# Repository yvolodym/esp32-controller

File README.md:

## Controller

ESP32-WROVER based wireless game controller. Two resistive (potentiometer)
analog joysticks plus an ST7789 SPI display, transmitting over ESP-NOW.
Firmware uses native ESP-IDF — see `CLAUDE.md` for architecture and pin
layout details.

### References

#### ESP-NOW
* https://randomnerdtutorials.com/esp32-cyd-esp-now-receive-data/
* https://habr.com/ru/companies/beget/articles/929336/
* https://wolles-elektronikkiste.de/esp-now
* https://github.com/SolderedElectronics/USB-UART-CH340C-converter-board-hardware-design

#### Joysticks (resistive thumbstick modules)
* https://tech.alpsalpine.com/e/products/detail/RKJXV122400R/
* https://github.com/dbenoy/thumbstick-breakout/blob/main/docs/board.png

#### LiPo charging module
* https://elektro.turanis.de/html/prj224/index.html

### Pin assignments

`CLAUDE.md` is the source of truth — the lists below are a quick reference.
All pins verified against `kicad/esp32-controller.kicad_sch` and
`kicad/supply.kicad_sch`.

#### ST7789 display (J1, 8-pin header — VSPI)

| J1 pin | Signal | GPIO |
|---|---|---|
| 1 | BL (backlight) | GPIO15 |
| 2 | CS  | GPIO5  |
| 3 | DC  | GPIO2  |
| 4 | RST | GPIO4  |
| 5 | MOSI / SDA | GPIO23 |
| 6 | SCK / SCL  | GPIO18 |
| 7 | VCC | +3.3 V |
| 8 | GND | GND |

#### Joystick 1 — RIGHT stick (U2 in schematic)

| Signal | GPIO | ADC |
|---|---|---|
| VRx (X axis) | GPIO32 | ADC1_CH4 |
| VRy (Y axis) | GPIO33 | ADC1_CH5 |
| Button (SEL) | GPIO25 | — *(not wired in hardware, see CLAUDE.md)* |

#### Joystick 2 — LEFT stick (U3 in schematic)

| Signal | GPIO | ADC |
|---|---|---|
| HRx (X axis) | GPIO34 | ADC1_CH6 |
| HRy (Y axis) | GPIO35 | ADC1_CH7 |
| Button (SEL) | GPIO26 | — *(not wired in hardware, see CLAUDE.md)* |

#### Battery sense

| Signal | GPIO | ADC |
|---|---|---|
| VBAT divider (R17 220 kΩ / R18 100 kΩ, net `HVBAT`) | GPIO36 (SENSOR_VP) | ADC1_CH0 |

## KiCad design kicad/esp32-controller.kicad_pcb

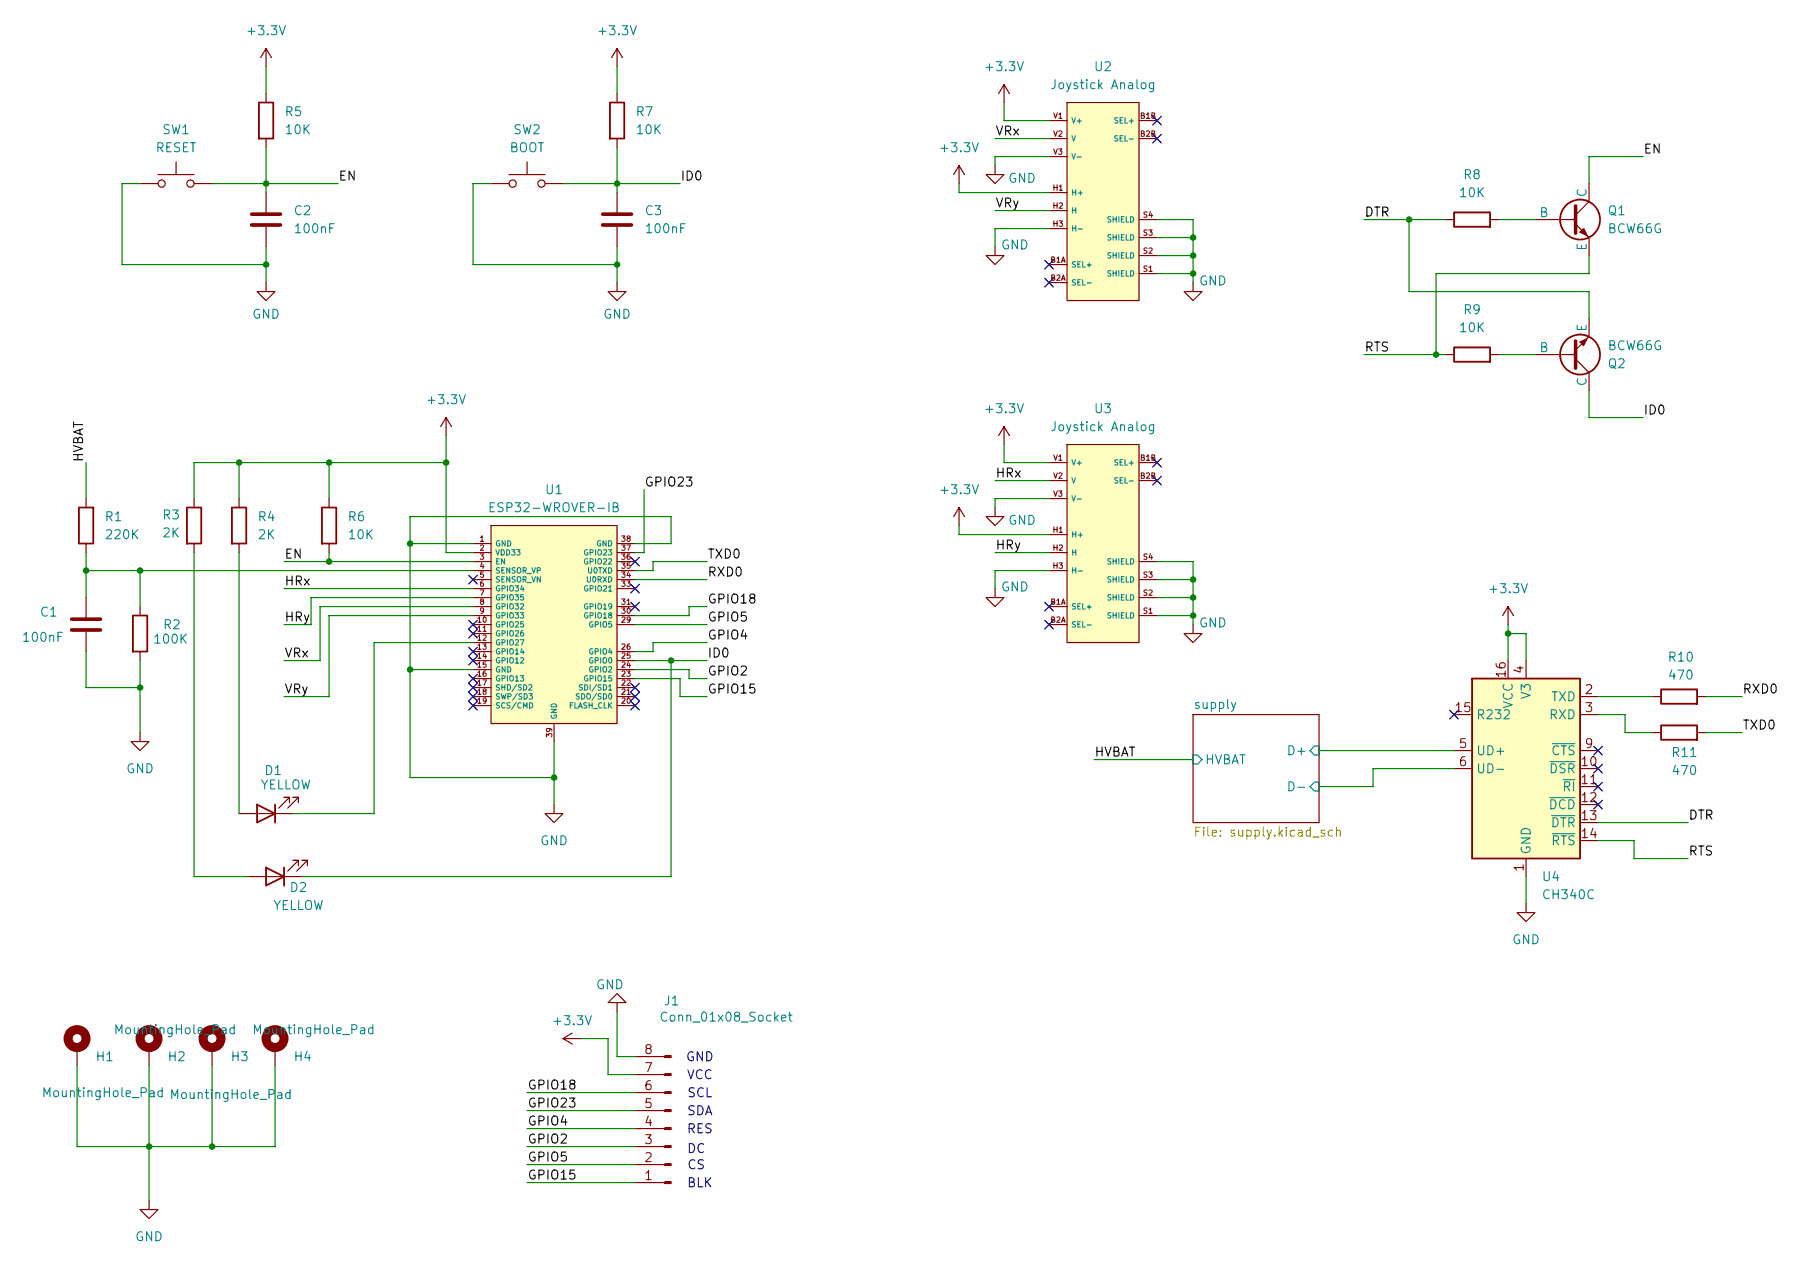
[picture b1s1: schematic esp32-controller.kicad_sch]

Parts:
C1, C2, C3: 100nF; C_1206_3216Metric
D1, D2: YELLOW; D_0603_1608Metric
H1, H2, H3, H4: MountingHole_Pad; MountingHole_2.7mm_Pad_Via
J1: Conn_01x08_Socket; PinSocket_1x08_P2.54mm_Vertical
Q1, Q2: BCW66G; SOT-23
R1: 220K; R_1206_3216Metric
R2: 100K; R_1206_3216Metric
R3, R4: 2K; R_1206_3216Metric
R5, R6, R7: 10K; R_1206_3216Metric
R8, R9: 10K; R_1206_3216Metric; LCSC C25819
R10, R11: 470; R_1206_3216Metric; LCSC C25819
SW1: RESET; SW_PUSH_1P1T_6x3.5mm_H4.3_APEM_MJTP1243
SW2: BOOT; SW_PUSH_1P1T_6x3.5mm_H4.3_APEM_MJTP1243
U1: ESP32-WROVER-IB
U2, U3: Joystick Analog; Joystick_Analog
U4: CH340C; SOIC-16_3.9x9.9mm_P1.27mm

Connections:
+3.3V: J1.7, R3.1, R4.1, R5.1, R6.1, R7.1, U1.2 (VDD33), U2.H1 (H+), U2.V1 (V+), U3.H1 (H+), U3.V1 (V+), U4.4 (V3), U4.16 (VCC); also elsewhere on the board
/DTR: Q2.3 (E), R8.1, U4.13 (~DTR)
/EN: C2.1, Q1.1 (C), R5.2, R6.2, SW1.2, U1.3 (EN)
/GPIO2: J1.3, U1.24 (GPIO2)
/GPIO4: J1.4, U1.26 (GPIO4)
/GPIO5: J1.2, U1.29 (GPIO5)
/GPIO15: J1.1, U1.23 (GPIO15)
/GPIO18: J1.6, U1.30 (GPIO18)
/GPIO23: J1.5, U1.37 (GPIO23)
/HRx: U1.6 (GPIO34), U3.V2 (V)
/HRy: U1.7 (GPIO35), U3.H2 (H)
/HVBAT: R1.2; also elsewhere on the board
/ID0: C3.1, D2.1 (K), Q2.1 (C), R7.2, SW2.2, U1.25 (GPIO0)
/RTS: Q1.3 (E), R9.1, U4.14 (~RTS)
/RXD0: R10.2, U1.34 (U0RXD)
/TXD0: R11.2, U1.35 (U0TXD)
/VRx: U1.8 (GPIO32), U2.V2 (V)
/VRy: U1.9 (GPIO33), U2.H2 (H)
/supply/D+: U4.5 (UD+); also elsewhere on the board
/supply/D-: U4.6 (UD-); also elsewhere on the board
GND: C1.2, C2.2, C3.2, H1.1, H2.1, H3.1, H4.1, J1.8, R2.2, SW1.1, SW2.1, U1.1 (GND), U1.15 (GND), U1.38 (GND), U1.39 (GND), U2.H3 (H-), U2.S1 (SHIELD), U2.S2 (SHIELD), U2.S3 (SHIELD), U2.S4 (SHIELD), U2.V3 (V-), U3.H3 (H-), U3.S1 (SHIELD), U3.S2 (SHIELD), U3.S3 (SHIELD), U3.S4 (SHIELD), U3.V3 (V-), U4.1 (GND); also elsewhere on the board
unnamed: D1.2 (A), R4.2
unnamed: D1.1 (K), U1.12 (GPIO27)
unnamed: D2.2 (A), R3.2
unnamed: Q1.2 (B), R8.2
unnamed: Q2.2 (B), R9.2
unnamed: C1.1, R1.1, R2.1, U1.4 (SENSOR_VP)
unnamed: R11.1, U4.3 (RXD)
unnamed: R10.1, U4.2 (TXD)

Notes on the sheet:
RES
VCC
SCL
GND
BLK
SDA

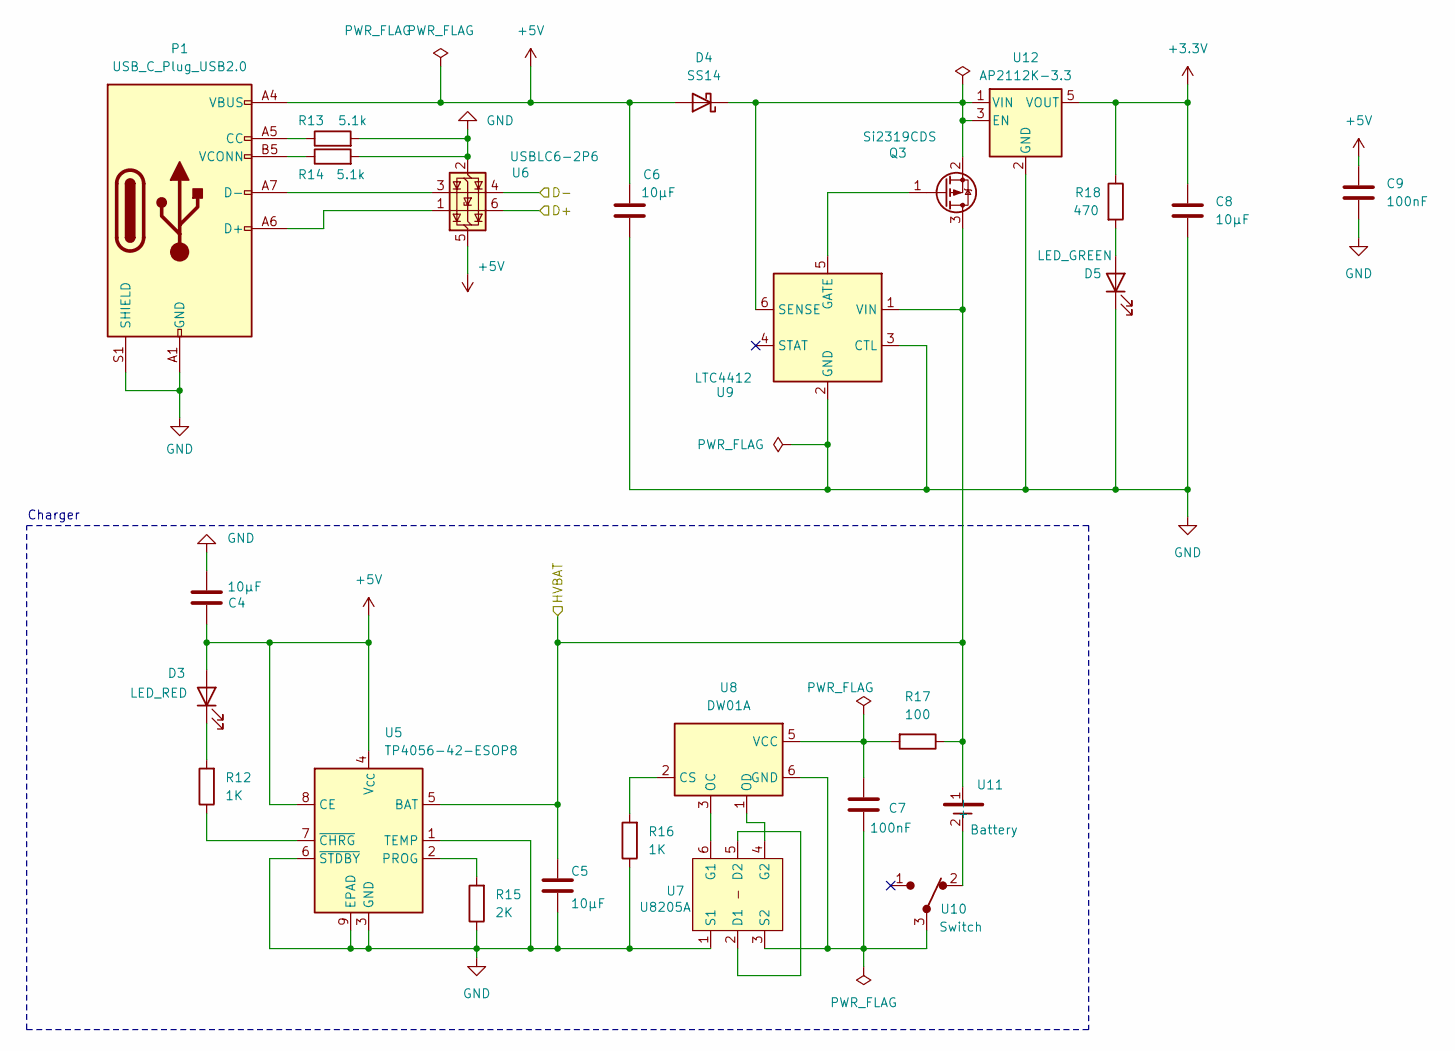
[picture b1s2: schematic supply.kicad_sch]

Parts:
C4, C5, C6, C8: 10µF; C_1206_3216Metric
C7, C9: 100nF; C_1206_3216Metric
D3: LED_RED; LED_D2.0mm_W4.8mm_H2.5mm_FlatTop
D4: SS14; D_SMA
D5: LED_GREEN; LED_D2.0mm_W4.8mm_H2.5mm_FlatTop
P1: USB_C_Plug_USB2.0; USB_C_Receptacle_GCT_USB4105-xx-A_16P_TopMnt_Horizontal; LCSC C456012
Q3: Si2319CDS; SOT-23
R12, R16: 1K; R_1206_3216Metric
R13, R14: 5.1k; R_1206_3216Metric
R15: 2K; R_1206_3216Metric
R17: 100; R_1206_3216Metric
R18: 470; R_1206_3216Metric
U5: TP4056-42-ESOP8; SOIC-8-1EP_3.9x4.9mm_P1.27mm_EP2.41x3.3mm_ThermalVias
U6: USBLC6-2P6; SOT-23-6
U7: U8205A; SOT-23-6
U8: DW01A; SOT-23-6
U9: LTC4412; TSOT-23-6
U10: Switch; SW_SPDT_PCM12
U11: Battery; NCR18650B
U12: AP2112K-3.3; SOT-23-5

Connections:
+3.3V: C8.1, R18.1, U12.5 (VOUT); also elsewhere on the board
+5V: C4.1, C6.1, C9.2, D3.2 (A), D4.2 (A), P1.A4 (VBUS), P1.A9 (VBUS), P1.B4 (VBUS), P1.B9 (VBUS), U5.4 (V_{CC}), U5.8 (CE), U6.5 (VBUS)
/HVBAT: C5.1, Q3.3 (D), R17.1, U5.5 (BAT), U9.1 (VIN), U11.1 (+); also elsewhere on the board
/supply/D+: U6.6 (I/O1); also elsewhere on the board
/supply/D-: U6.4 (I/O2); also elsewhere on the board
GND: C4.2, C5.2, C6.2, C8.2, C9.1, D5.1 (K), P1.A1 (GND), P1.A12 (GND), P1.B1 (GND), P1.B12 (GND), P1.S1 (SHIELD), R13.2, R14.2, R15.1, R16.1, U5.1 (TEMP), U5.3 (GND), U5.6 (~STDBY), U5.9 (EPAD), U6.2 (GND), U7.1 (S1), U9.2 (GND), U9.3 (CTL), U12.2 (GND); also elsewhere on the board
unnamed: D3.1 (K), R12.2
unnamed: D4.1 (K), Q3.2 (S), U9.6 (SENSE), U12.1 (VIN), U12.3 (EN)
unnamed: D5.2 (A), R18.2
unnamed: P1.A5 (CC), R13.1
unnamed: P1.A6 (D+), U6.1 (I/O1)
unnamed: P1.A7 (D-), U6.3 (I/O2)
unnamed: P1.B5 (VCONN), R14.1
unnamed: Q3.1 (G), U9.5 (GATE)
unnamed: R15.2, U5.2 (PROG)
unnamed: R12.1, U5.7 (~CHRG)
unnamed: U7.2 (D1), U7.5 (D2)
unnamed: U7.6 (G1), U8.3 (OC)
unnamed: U7.4 (G2), U8.1 (OD)
unnamed: C7.1, U7.3 (S2), U8.6 (GND), U10.3
unnamed: R16.2, U8.2 (CS)
unnamed: C7.2, R17.2, U8.5 (VCC)
unnamed: U10.2, U11.2 (-)

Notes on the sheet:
Charger

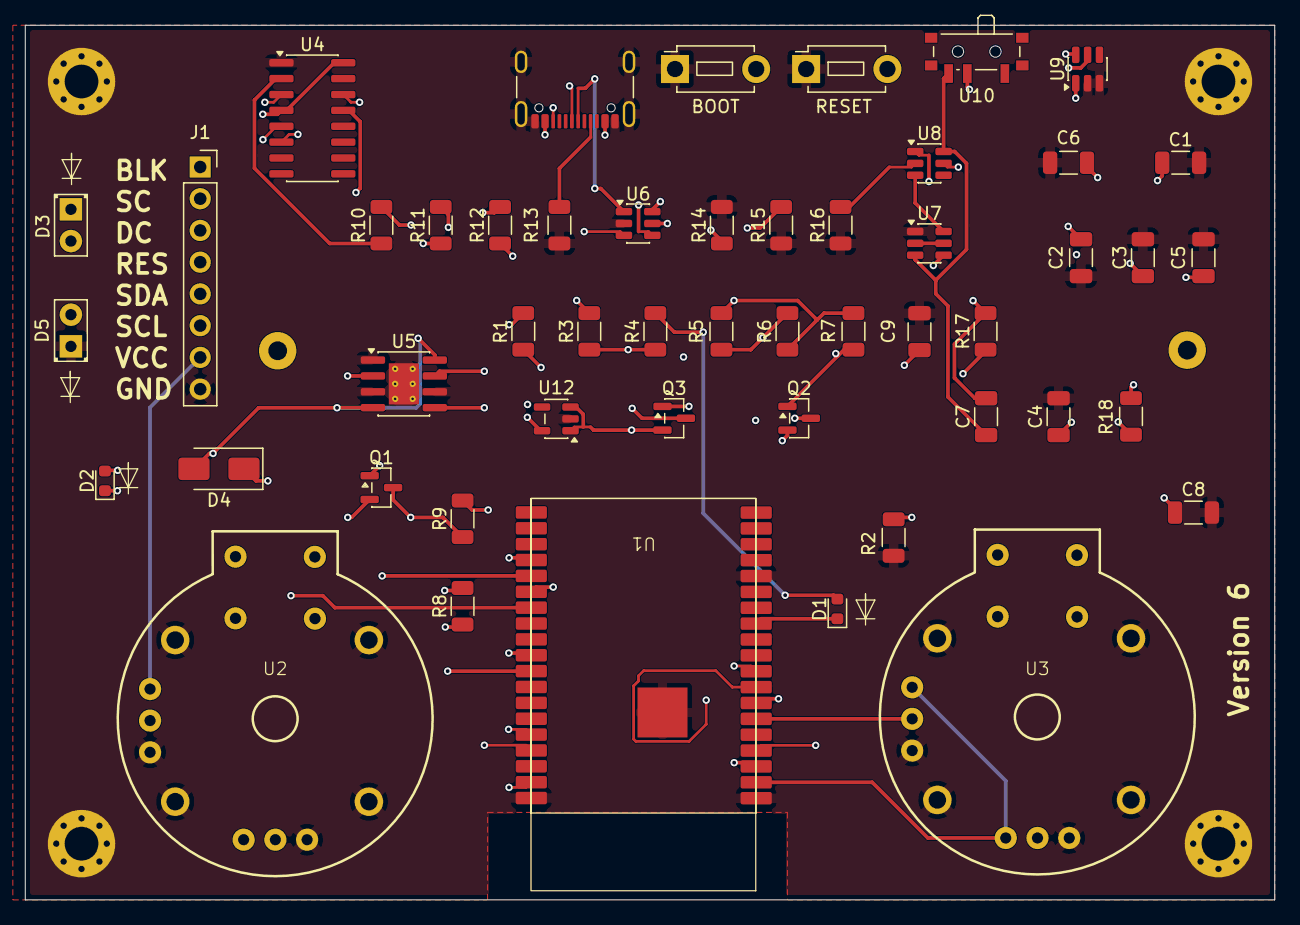
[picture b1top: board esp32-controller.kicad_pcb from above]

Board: 4 copper layers, 100.0 x 70.0 mm, 55 parts (1 on the bottom side), 47 nets.

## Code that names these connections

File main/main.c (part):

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
// ========== CONFIGURATION ========== //
// Joystick 1 (U2 in schematic, net /VRx /VRy)
#define JOY1_X_PIN ADC_CHANNEL_4  // GPIO32 - X-axis joystick 1
#define JOY1_Y_PIN ADC_CHANNEL_5  // GPIO33 - Y-axis joystick 1
// Joystick 2 (U3 in schematic, net /HRx /HRy)
#define JOY2_X_PIN ADC_CHANNEL_6  // GPIO34 - X-axis joystick 2
#define JOY2_Y_PIN ADC_CHANNEL_7  // GPIO35 - Y-axis joystick 2
// Joystick buttons
#define JOY1_BTN_PIN GPIO_NUM_25  // Joystick 1 button
#define JOY2_BTN_PIN GPIO_NUM_26  // Joystick 2 button
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
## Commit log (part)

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2025-07-28 init
2025-12-09 Add Joystik section to README
    Added a new section for Joystik with a relevant link.
2025-12-30 Update README with additional joystick resources
    Added links for Hall TMR joystick electrical properties and PS5 hall joysticks.
2025-12-30 Add link to thumbstick breakout board image
2026-05-07 GA install
2026-05-25 docu
2026-05-27 tester
